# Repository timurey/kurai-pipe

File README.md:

# KURAI Pipe

Solar-powered Meshtastic node on LTO cells, built to slide into a 50 mm pipe.

KURAI Pipe is a rework of the [MASN V2.0 HT-RA62](https://github.com/danielcharrua/masn-meshtastic-autonomous-solar-node) board by Daniel Pereyra Costas (EA1REX). The radio (HT-RA62 / SX1262) and the nice!nano-compatible ProMicro nRF52840 stay; the power path, the board shape and the connectors are new.

> **Status:** work in progress. This repository holds the KiCad sources only. There is no fabrication output yet, and the PCB still has to be updated from the schematic — see [TODO.md](TODO.md) for the open items.

## Features

- 39 × 99 mm board (under the 100 mm price step), three M2.5 mounting holes, fits a 50 mm pipe
- 1S (2.7 V) or 2S (5.4 V) LTO pack; 1S Na-ion is also possible — **no 2S Li-ion or 2S Na-ion**
- SD30CRMA (CN3795) MPPT charger module with a trimmer-set charge voltage
- TPS63802 buck-boost module (set to 4.2 V) feeding the MCU; the ProMicro's own 3.3 V LDO powers the radio and sensors
- JP1 "2S DIRECT" to bypass the converter on 2S builds without the module
- HT-RA62 (SX1262) LoRa module on flat SMD pads
- INA3221 (panel / MPPT output / battery) and BME280 on the bottom side
- I2C header, second-serial wire pads, RESET and USER buttons
- BLE antenna keepout zone
- Assembly notes on the silkscreen (Russian)

## Power path

```
solar panel ──► SD30CRMA (CN3795, MPPT) ──► LTO pack 1S/2S ──► TPS63802 (4.2 V) ──► ProMicro B+ ──► 3.3 V LDO ──► HT-RA62, INA3221, BME280
```

The ProMicro/nice!nano has its own regulator between B+ and the 3.3 V rail. Feeding B+ with 3.3 V leaves that regulator in dropout — the rail sags to about 3.0 V, which costs radio output power. 4.2 V gives the regulator enough headroom while dissipating less than 5 V would (a 330 kΩ resistor across the TPS63802 module's voltage-select pads sets 4.2 V; the module leaves the factory at 5 V).

On a 1S pack the converter is required. On 2S the converter is optional: without it, close JP1 "2S DIRECT" to feed B+ straight from the pack. Never close JP1 with the TPS63802 module fitted.

## Connectors

| Ref | What | Pins |
| --- | --- | --- |
| J1 | I2C header, 2.54 mm THT | GND, +3.3 V, SCL, SDA |
| J3 | Second serial port pads, 2.54 mm SMD | GND, +3.3 V, TX (P0.08), RX (P0.06) |
| SOLAR, BATTERY | Screw terminals, 5.08 mm | +, − |
| SOLAR_SW1, NODE_SW1 | SS12D10 slide switches | — |

J3 is a set of solder pads, not a header, and is excluded from the BOM/CPL. TX/RX cross over: the MCU's TX goes to the module's RX.

There are no pads for a GPS module: P0.20/P0.22 stay free, so a GNSS receiver has to be wired to the MCU by hand if needed.

## Firmware

A Meshtastic build for this board lives in the author's fork, with the environment `nrf52_promicro_diy-solar-lto-2s`:

- low-battery cutoff and wake-up are handled in firmware (LPCOMP) — there is no hardware supervisor;
- the variant has `MESHTASTIC_EXCLUDE_GPS` and `MESHTASTIC_EXCLUDE_SERIAL` set; remove the serial one before J3 is usable, and the GPS one as well if you wire a receiver by hand;
- the INA3221 channel labels in the MASN footprint are swapped relative to a CJMCU-3221 module, so the battery is on CH3 and the panel on CH1.

## Assembly notes

These are repeated on the bottom silkscreen (in Russian), because they are easy to get wrong:

- Set the SD30CRMA charge voltage with the ADJ trimmer **before** connecting the pack: 2.70 V for 1S LTO, 5.40 V for 2S LTO, 3.95 V for 1S Na-ion.
- MPPT resistor on the SD30CRMA: 16 kΩ for a 9 V panel, 22.1 kΩ for a 12 V panel.
- Pack voltage must not exceed 5.5 V. 2S Li-ion and 2S Na-ion are not allowed.
- Re-solder the SD30CRMA electrolytics lying flat, or the module will not fit the pipe.
- INA3221 must be the version with separate + and − per channel. A module with a common − will short the panel to the battery through the shunt.
- BME280: either the 6-pin or the 4-pin module fits the footprint.
- Battery voltage divider: 1 MΩ / 1 MΩ to P0.31.
- All modules and SMD parts are mounted flat; the INA3221 and BME280 go on the bottom side.

## Repository layout

```
pcb/kurai-pipe/
  NOTICE.md                modification notice and attribution (CERN-OHL-S v2)
  kicad/
    kurai-pipe.kicad_pro/.kicad_sch/.kicad_pcb
    masn.pretty/           project footprint library
    masn.3dshapes/         3D models used by the board
LICENSE.txt                CERN-OHL-S v2
TODO.md                    open items
```

Open `pcb/kurai-pipe/kicad/kurai-pipe.kicad_pro` with **KiCad 10.0 or newer** (the files are saved in the KiCad 10 format). The project libraries are local, so no extra installation is needed.

## Fabrication

Gerbers, drill files, BOM, pick-and-place and STEP export are not published yet. They will be added once the PCB is updated from the schematic and checked with DRC at the fab limits.

## Credits and licence

KURAI Pipe is based on MASN V2.0 HT-RA62 by Daniel Pereyra Costas (EA1REX), released under the CERN Open Hardware Licence v2 — Strongly Reciprocal. The original notices are kept in the PCB file and in [NOTICE.md](pcb/kurai-pipe/NOTICE.md), and the licence notice is on the bottom silkscreen.

This modified design is licensed under CERN-OHL-S v2 as well; the full text is in [LICENSE.txt](LICENSE.txt). It is provided **without any express or implied warranty** — you build and deploy your own node at your own risk, and you are responsible for complying with local radio regulations.

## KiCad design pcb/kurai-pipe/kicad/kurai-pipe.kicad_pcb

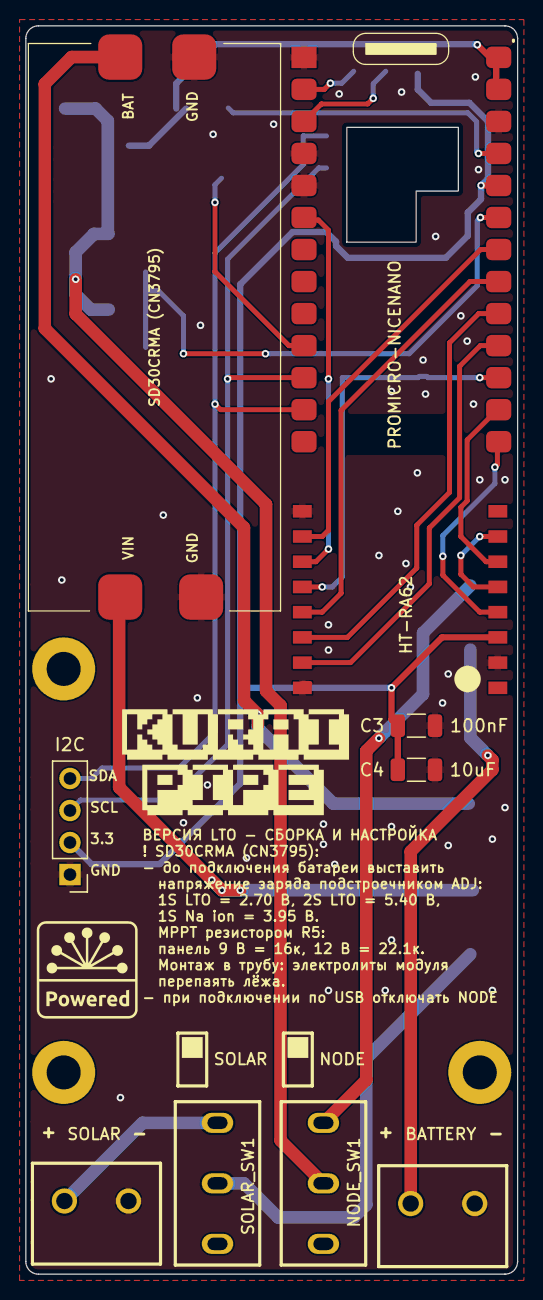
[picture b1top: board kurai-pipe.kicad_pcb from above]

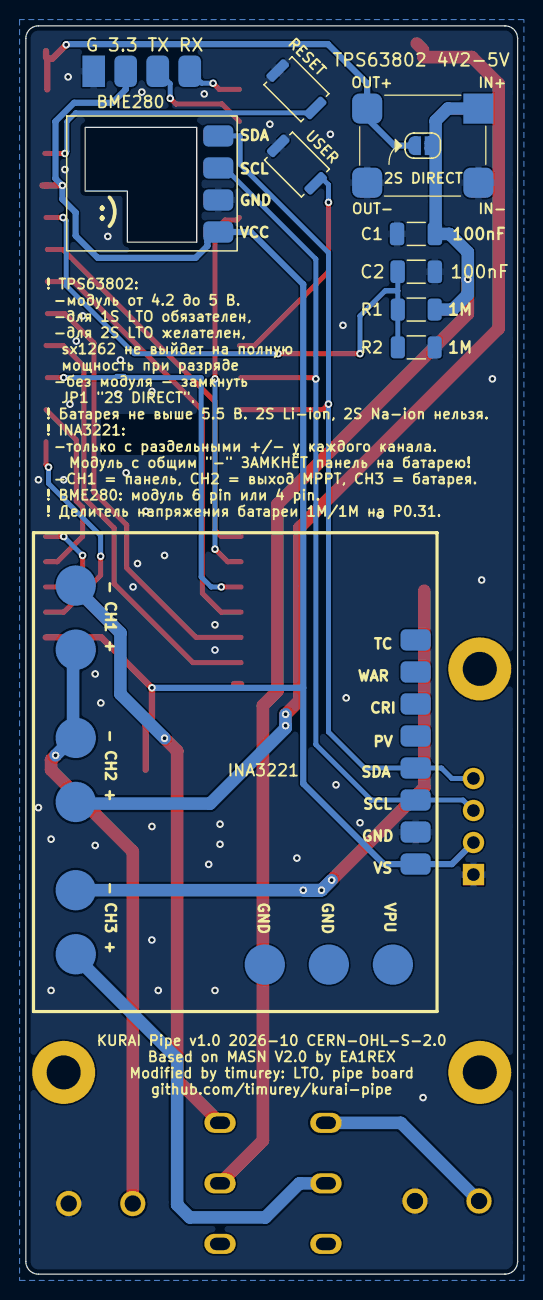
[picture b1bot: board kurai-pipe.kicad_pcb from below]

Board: 2 copper layers, 39.0 x 99.0 mm, 26 parts (11 on the bottom side), 26 nets.

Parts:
BATTERY: PA001-2P; CONN-TH_2P-P5.08_PA001-2P
BME280: BME280; GY-BME280_4pin_SMD
C1, C2, C3: 100nF; C_1206_3216Metric
C4: 10uF; C_1206_3216Metric
CN3795: SD30CRMA (CN3795 MPPT); SD30CRMA_CN3795_45x20mm_SMD
H1, H2, H3: M2.5; MountingHole_2.7mm_M2.5_Pad_D5.0
HT-RA62: HT-RA62; WIRELM-SMD_HT-RA62
J1: I2C; PinHeader_1x04_P2.54mm_Vertical
J3: SERIAL2; Pads_1x04_P2.54mm_SMD
JP1: 2S DIRECT; SolderJumper-2_P1.3mm_Open_RoundedPad1.0x1.5mm
LOGO**: Logo_KURAI_PIPE_2line
LOGO**#2: Logo_KuraiPowered_8mm
NODE_SW1: SS12D10-ZG5; SW-TH_3P-L12.7-W6.7-P4.80_SS12D10-ZGXX
PROMICRO-NICENANO: promicro nrf52840 - nicenano compatible; NICENANO_SMD
R1, R2: 1M; R_1206_3216Metric
SOLAR: PA001-2P; CONN-TH_2P-P5.08_PA001-2P
SOLAR_SW1: SS12D10-ZG5; SW-TH_3P-L12.7-W6.7-P4.80_SS12D10-ZGXX
SW1: RESET; SW_Push_SPST_NO_Alps_SKRK
SW2: USER; SW_Push_SPST_NO_Alps_SKRK
U1: INA3221; INA3221-PCB-V1_SMD
U5: TPS63802 4V2-5V; TPS63802_Jessinie_10x8mm_SMD

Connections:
+3.3V: BME280.1 (VCC), C3.1, C4.1, HT-RA62.3 (3V3), J1.2, J3.2, PROMICRO-NICENANO.22 (3.3V), U1.1 (VS)
BAT+: C1.1, JP1.1 (A), NODE_SW1.2, R1.2, U5.1 (IN+)
BATTERY_POSSITIVE: BATTERY.1, U1.10 (CH1_+), U1.11 (CH2_-)
BUSY: HT-RA62.10 (BUSY), PROMICRO-NICENANO.20 (P0.29)
CS: HT-RA62.15 (NSS), PROMICRO-NICENANO.17 (P1.13)
DIO1: HT-RA62.6 (DIO1), PROMICRO-NICENANO.15 (P0.10)
GND: BATTERY.2, BME280.2 (GND), C1.2, C2.2, C3.2, C4.2, CN3795.2 (GND), CN3795.3 (GND), HT-RA62.2 (GND), HT-RA62.9 (GND), HT-RA62.16 (GND), J1.1, J3.1, PROMICRO-NICENANO.1 (GND), PROMICRO-NICENANO.4 (GND), PROMICRO-NICENANO.5 (GND), PROMICRO-NICENANO.24 (GND), R2.1, SOLAR.2, SW1.2, SW2.2, U1.2 (GND), U5.2 (IN-), U5.3 (OUT-)
MISO: HT-RA62.13 (MISO), PROMICRO-NICENANO.19 (P0.02)
MOSI: HT-RA62.14 (MOSI), PROMICRO-NICENANO.18 (P1.15)
MPPT_CHARGER_BAT: CN3795.4 (BAT), U1.12 (CH2_+)
MPPT_CHARGER_VIN: CN3795.1 (VIN), U1.13 (CH3_-)
NICENANO_BATTERY: NODE_SW1.3, U1.9 (CH1_-)
unnamed: HT-RA62.5 (TXEN), HT-RA62.7 (DIO2)
RESET: PROMICRO-NICENANO.23 (RESET), SW1.1
RST: HT-RA62.4 (RST), PROMICRO-NICENANO.14 (P0.09)
RXEN: HT-RA62.11 (RXEN), PROMICRO-NICENANO.6 (P0.17)
SCK: HT-RA62.12 (SCK), PROMICRO-NICENANO.16 (P1.11)
SCL: BME280.3 (SCL), J1.3, PROMICRO-NICENANO.11 (P0.11), U1.3 (SCL)
SDA: BME280.4 (SDA), J1.4, PROMICRO-NICENANO.12 (P1.04), U1.4 (SDA)
SER2_RX: J3.4, PROMICRO-NICENANO.2 (P0.06)
SER2_TX: J3.3, PROMICRO-NICENANO.3 (P0.08)
SOLAR_PANEL_POSSITIVE: SOLAR_SW1.2, U1.14 (CH3_+)
SOLAR_PANEL_POSSITIVE_IN: SOLAR.1, SOLAR_SW1.3
USER_BTN: PROMICRO-NICENANO.10 (P1.00), SW2.1
VBAT_ADC: C2.1, PROMICRO-NICENANO.21 (P0.31), R1.1, R2.2
VCC_MCU: JP1.2 (B), PROMICRO-NICENANO.25 (BAT+), PROMICRO-NICENANO.26 (BAT+), U5.4 (OUT+)

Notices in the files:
pcb/kurai-pipe/kicad/kurai-pipe.kicad_pcb:
Licensed under CERN-OHL-S v2 (see LICENSE.txt), provided WITHOUT ANY WARRANTY
KURAI Pipe v1.0 2026-10 CERN-OHL-S-2.0
